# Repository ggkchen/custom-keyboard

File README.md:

# Custom Keyboard

This is a keyboard shortened mainly to optimize mouse space for Valorant while keeping enough keys to everyday computer use. It uses an arduino micro pro as a microcontroller
and Kailh Box Thick Clicky switches. PCB is not hot swappable but should be simple to mount microcontroller, switches and keycaps onto it. The case has minimal parts for easy
lightweight assembly. Arrow keys have been replaced to serve as customizable macros or other special functions.

# PCB

# CAD ASSEMBLY

Onshape Link: https://cad.onshape.com/documents/7541f2100a52e2a8fb9d96d0/w/174a04ea7bc7f7ecaec00ce4/e/b31f0979a24da6a144661240?renderMode=0&uiState=699c00031957867eacc0531d

# BOM

| Item       | Part                       | Qty | Source             | Unit (USD) | Total (USD) | Description                                     |
| ---------- | -------------------------- | --- | ------------------ | ---------- | ----------- | ----------------------------------------------- |
| Switches   | [Navy-CPG1511F01S09][sw]   | 110 | Kailh              | 0.65       | 71.23       | Kailh Box Thick Clicky switches                 |
| Diodes     | [1N4148FS-ND][di]          | 70  | Digikey (onsemi)   | 0.04       | 2.73        | 1N4148 switching diodes for the matrix          |
| Controller | [Arduino Pro Micro][mc]    | 1   | AliExpress         | 5.33       | 5.33        | ATmega32U4 Pro Micro board                      |
| PCB        | HackPad PCB                | 5   | JLCPCB             | 5.43       | 27.17       | Custom PCB (JLCPCB minimum order qty 5)         |
| Keycaps    | [Blank PBT ANSI Set][kc]   | 1   | AliExpress         | 15.00      | 15.00       | 64-key blank PBT ANSI set, 6.25u spacebar       |
|            |                            |     | **Grand Total**    |            | **121.46**  |                                                 |

[sw]: https://www.kailh.net/products/kailh-box-thick-clicky-switch-set?variant=43650830369010
[di]: https://www.digikey.com/en/products/detail/onsemi/1N4148/458603
[mc]: https://www.aliexpress.com/ssr/300000512/BundleDeals2
[kc]: https://www.aliexpress.com/wholesale?SearchText=blank+pbt+keycaps+ansi+60+percent

Keycap set must include: 6.25u spacebar, 2u Backspace, 2u L-Shift, 2.25u Enter, 1.75u Caps, 1.5u Tab + Backslash, 1.25u modifiers. Any standard 60%/64-key ANSI kit works.

# Build Guide

Heads up before you start: this whole build took me a weekend, but most of that was waiting for parts. Actual hands-on time is maybe 4–5 hours if you're slow with a soldering iron like me.

## Stuff you need

Parts are all in the BOM up there. Beyond that you'll want:

- soldering iron + solder (any decent iron works, I used a TS100)
- flush cutters for trimming diode legs
- tweezers — really helpful for placing diodes, get a pair if you don't have one
- some masking tape

You'll also need a printed case. STL is in `CAD/KEEBASSEMBLY.stl`, or grab the STEP if you want to tweak it. I printed mine in PETG at 0.2 layer height and it was fine.

## 1. Get the PCB made

The gerbers are sitting in `PCB/kicad/gerbers/Keyboard Gerbers.zip`. Just upload that zip to JLCPCB, and order 5.

## 2. Solder the diodes

The diodes are directional, so the black band on the diode lines up with the **square pad** on the PCB. If the diode is facing the wrong direction the key won't work, or it will register the wrong keys.

What worked for me:
- bend all 64 diodes into little staples first, in a batch
- drop them all into the board before soldering anything (saves you from picking up the iron 64 separate times)
- tape something flat over the back, flip the board, and the diodes will sit flush from gravity
- solder one leg of each, do a pass for alignment, then solder the other legs
- snip the leads when you're done
  
## 3. Solder the Pro Micro

Do the Pro Micro **before** the switches.

## 4. Switches

Push 4 switches into the corners, and one in the middle. These hold everything in place, then flip it, and solder just those 5. After that, keep putting switches in and solder them in.

# Firmware

Runs QMK. The `keyboard.json` and `keymap.c` are in `Keyboard_firmware/`. There are three layers:

- base — normal typing
- fn (hold the key in the bottom right corner where you'd expect right-arrow) — gives you F1–F12, PrtSc, Pause, and the missing arrow nav keys
- reset (fn + the second mod key) — hitting `R` on this layer puts the board into the bootloader, so you can re-flash without opening the case

## Setting up QMK

If you've never used QMK before:

```
python3 -m pip install --user qmk
qmk setup
```

Hit yes when it asks to clone `qmk_firmware` to your home directory.

## Copy the files in

QMK expects keyboards to live under `qmk_firmware/keyboards/`, so:

```
mkdir -p ~/qmk_firmware/keyboards/keeb/keymaps/default
cp Keyboard_firmware/keyboard.json ~/qmk_firmware/keyboards/keeb/keyboard.json
cp Keyboard_firmware/keymap.c       ~/qmk_firmware/keyboards/keeb/keymaps/default/keymap.c
```

## Compile

```
qmk compile -kb keeb -km default
```

Should drop a `.hex` in the QMK root after a few seconds. If it complains about `LAYOUT_64_ansi` not existing, your `keyboard.json` didn't make it over — re-check the copy.

## Flash

Plug the keyboard in, then:

```
qmk flash -kb keeb -km default
```

When it says `Detecting USB port, reset your controller now...`, you've got about 8 seconds to short the `RST` pin to `GND` on the Pro Micro twice in quick succession. Tweezers work. The flasher will grab it and write the firmware.

If you ever brick the keymap and lose access to your reset key, the layer-2 bootloader binding saves you — fn + mod + `R`. So even if you mess up the keymap badly, you can always get back into the bootloader without cracking the case open.

To customize anything — different keys, macros on the arrow positions, whatever — edit `keymap.c` and rerun the compile + flash steps.

# Testing

Don't put the keycaps on yet.

**1. Plug it in.** The little power LED on the Pro Micro should come on. If it doesn't, unplug right away and look for solder bridges between adjacent pins on the Pro Micro.

**2. Check that the OS sees it.** On Windows it'll show up under Keyboards in Device Manager. On Mac you'll get the keyboard identification wizard popping up — just close it. On Linux, `lsusb` will show a `feed:0000` device. (That's the default VID/PID baked into the firmware, no, it's not malware.)

**3. Hit every key.** https://config.qmk.fm/#/test is what I use. Press each key, check it lights up on screen, move on.

If something's wrong, it's almost always one of these:
- one key does nothing → cold joint, reflow both pins
- one key types something else → either a solder bridge between two switches, or a diode flipped on a different key (matrix scanning makes this confusing)
- a whole row or column is dead → cold joint at the Pro Micro pin for that row/col, or a totally fried diode somewhere on the row
- pressing one key triggers two → diode missing or backwards on one of them (the matrix can't isolate without it)
- nothing at all → firmware didn't flash, or you're holding a perfectly good paperweight

**4. Test the fn layer.** Hold the fn key (bottom-right area, next to up-arrow) and tap the number row — should give you F1 through F12.

**5. Test the bootloader combo.** fn + the second mod + `R`. The keyboard should disappear from your machine and reappear as `Arduino Leonardo` or similar. Unplug and replug and you're back to normal. Once you've confirmed this works, you can flash new firmware forever without touching the reset pins again.

That's it. Keycaps on, screw the case shut, go play Valorant.

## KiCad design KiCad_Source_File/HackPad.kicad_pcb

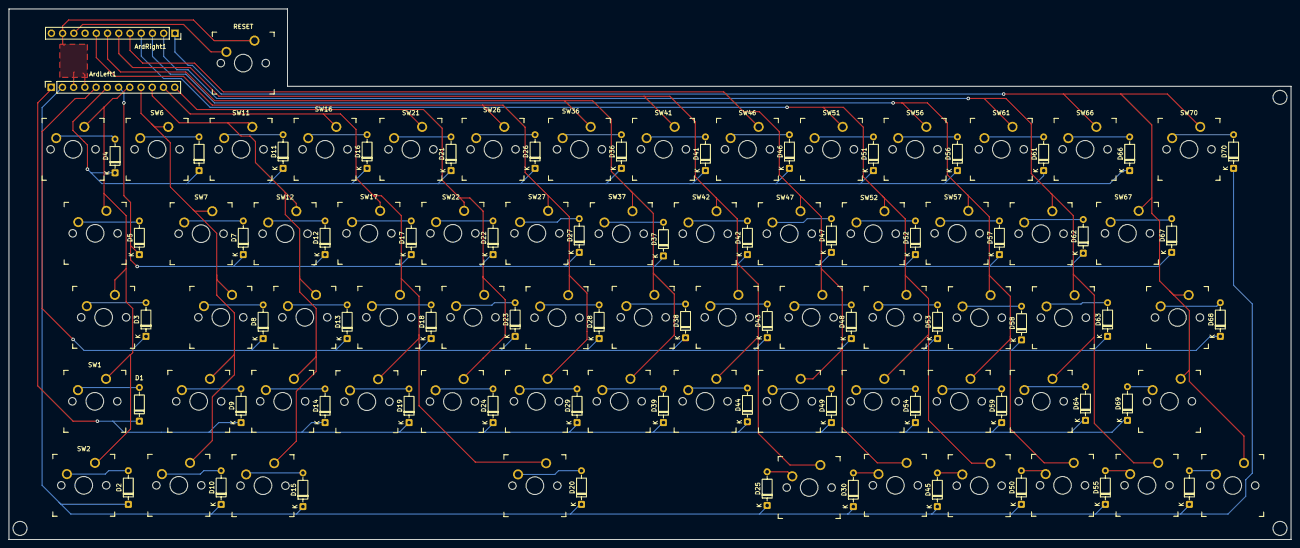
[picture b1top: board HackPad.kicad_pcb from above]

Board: 2 copper layers, 290.0 x 120.0 mm, 129 parts (0 on the bottom side), 83 nets.

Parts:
ArdLeft1: Conn_01x12_Socket; PinSocket_1x12_P2.54mm_Vertical
ArdRight1: Conn_01x12_Socket; PinSocket_1x12_P2.54mm_Vertical
D1, D2, D3, D4, D5, D6, D7, D8, D9, D10, D11, D12, D13, D14, D15, D16, D17, D18, D19, D20, D21, D22, D23, D24, D25, D26, D27, D28, D29, D30, D36, D37, D38, D39, D41, D42, D43, D44, D45, D46, D47, D48, D49, D50, D51, D52, D53, D54, D55, D56, D57, D58, D59, D60, D61, D62, D63, D64, D66, D67, D68, D69, D70: 1N4148; D_DO-35_SOD27_P7.62mm_Horizontal
RESET: SW_MX
SW1, SW2, SW3, SW4, SW5, SW6, SW7, SW8, SW9, SW10, SW11, SW12, SW13, SW14, SW15, SW16, SW17, SW18, SW19, SW20, SW21, SW22, SW23, SW24, SW25, SW26, SW27, SW28, SW29, SW30, SW36, SW37, SW38, SW39, SW41, SW42, SW43, SW44, SW45, SW46, SW47, SW48, SW49, SW50, SW51, SW52, SW53, SW54, SW55, SW56, SW57, SW58, SW59, SW60, SW61, SW62, SW63, SW64, SW66, SW67, SW68, SW69, SW70: SW_Push; SW_MX

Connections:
/C1: ArdLeft1.8, SW1.1, SW2.1, SW3.1, SW4.1, SW5.1
/C2: ArdLeft1.9, SW6.1, SW7.1, SW8.1, SW9.1, SW10.1
/C3: ArdLeft1.10, SW11.1, SW12.1, SW13.1, SW14.1, SW15.1
/C4: ArdLeft1.11, SW16.1, SW17.1, SW18.1, SW19.1, SW20.1
/C5: ArdLeft1.12, SW21.1, SW22.1, SW23.1, SW24.1
/C6: ArdRight1.8, SW26.1, SW27.1, SW28.1, SW29.1
/C7: ArdRight1.7, SW36.1, SW37.1, SW38.1, SW39.1
/C8: ArdRight1.6, SW25.1, SW41.1, SW42.1, SW43.1, SW44.1
/C9: ArdRight1.5, SW30.1, SW46.1, SW47.1, SW48.1, SW49.1
/C10: ArdRight1.4, SW45.1, SW51.1, SW52.1, SW53.1, SW54.1
/C11: ArdRight1.3, SW50.1, SW56.1, SW57.1, SW58.1, SW59.1
/C12: ArdRight1.2, SW55.1, SW61.1, SW62.1, SW63.1, SW64.1
/C13: ArdRight1.1, SW60.1, SW66.1, SW67.1, SW68.1, SW69.1, SW70.1
/R1: ArdLeft1.1, D1.1 (K), D9.1 (K), D14.1 (K), D19.1 (K), D24.1 (K), D29.1 (K), D39.1 (K), D44.1 (K), D49.1 (K), D54.1 (K), D59.1 (K), D64.1 (K), D69.1 (K)
/R2: ArdLeft1.2, D2.1 (K), D10.1 (K), D15.1 (K), D20.1 (K), D25.1 (K), D30.1 (K), D45.1 (K), D50.1 (K), D55.1 (K), D60.1 (K), D70.1 (K)
/R3: ArdLeft1.5, D3.1 (K), D8.1 (K), D13.1 (K), D18.1 (K), D23.1 (K), D28.1 (K), D38.1 (K), D43.1 (K), D48.1 (K), D53.1 (K), D58.1 (K), D63.1 (K), D68.1 (K)
/R4: ArdLeft1.6, D4.1 (K), D6.1 (K), D11.1 (K), D16.1 (K), D21.1 (K), D26.1 (K), D36.1 (K), D41.1 (K), D46.1 (K), D51.1 (K), D56.1 (K), D61.1 (K), D66.1 (K)
/R5: ArdLeft1.7, D5.1 (K), D7.1 (K), D12.1 (K), D17.1 (K), D22.1 (K), D27.1 (K), D37.1 (K), D42.1 (K), D47.1 (K), D52.1 (K), D57.1 (K), D62.1 (K), D67.1 (K)
/RST: ArdRight1.10, RESET.2
GND: ArdLeft1.3, ArdLeft1.4, ArdRight1.11, RESET.1
unnamed: D1.2 (A), SW1.2
unnamed: D2.2 (A), SW2.2
unnamed: D3.2 (A), SW3.2
unnamed: D4.2 (A), SW4.2
unnamed: D5.2 (A), SW5.2
unnamed: D6.2 (A), SW6.2
unnamed: D7.2 (A), SW7.2
unnamed: D8.2 (A), SW8.2
unnamed: D9.2 (A), SW9.2
unnamed: D10.2 (A), SW10.2
unnamed: D11.2 (A), SW11.2
unnamed: D12.2 (A), SW12.2
unnamed: D13.2 (A), SW13.2
unnamed: D14.2 (A), SW14.2
unnamed: D15.2 (A), SW15.2
unnamed: D16.2 (A), SW16.2
unnamed: D17.2 (A), SW17.2
unnamed: D18.2 (A), SW18.2
unnamed: D19.2 (A), SW19.2
unnamed: D20.2 (A), SW20.2
unnamed: D21.2 (A), SW21.2
unnamed: D22.2 (A), SW22.2
unnamed: D23.2 (A), SW23.2
unnamed: D24.2 (A), SW24.2
unnamed: D25.2 (A), SW25.2
unnamed: D26.2 (A), SW26.2
unnamed: D27.2 (A), SW27.2
unnamed: D28.2 (A), SW28.2
unnamed: D29.2 (A), SW29.2
unnamed: D30.2 (A), SW30.2
unnamed: D36.2 (A), SW36.2
unnamed: D37.2 (A), SW37.2
unnamed: D38.2 (A), SW38.2
unnamed: D39.2 (A), SW39.2
unnamed: D41.2 (A), SW41.2
unnamed: D42.2 (A), SW42.2
unnamed: D43.2 (A), SW43.2
unnamed: D44.2 (A), SW44.2
unnamed: D45.2 (A), SW45.2
unnamed: D46.2 (A), SW46.2
unnamed: D47.2 (A), SW47.2
unnamed: D48.2 (A), SW48.2
unnamed: D49.2 (A), SW49.2
unnamed: D50.2 (A), SW50.2
unnamed: D51.2 (A), SW51.2
unnamed: D52.2 (A), SW52.2
unnamed: D53.2 (A), SW53.2
unnamed: D54.2 (A), SW54.2
unnamed: D55.2 (A), SW55.2
unnamed: D56.2 (A), SW56.2
unnamed: D57.2 (A), SW57.2
unnamed: D58.2 (A), SW58.2
unnamed: D59.2 (A), SW59.2
unnamed: D60.2 (A), SW60.2
unnamed: D61.2 (A), SW61.2
unnamed: D62.2 (A), SW62.2
unnamed: D63.2 (A), SW63.2
unnamed: D64.2 (A), SW64.2
unnamed: D66.2 (A), SW66.2
unnamed: D67.2 (A), SW67.2
unnamed: D68.2 (A), SW68.2
unnamed: D69.2 (A), SW69.2
unnamed: D70.2 (A), SW70.2

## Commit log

2026-04-30 initial commit
    put all the files in
2026-04-30 Create Valorant.png
    POSTER
2026-04-30 Add poster image to README and update table
2026-04-30 made more readable and updated README
2026-05-07 updated code
2026-05-09 added poster and changed BOM
2026-05-09 reorganized pcb
